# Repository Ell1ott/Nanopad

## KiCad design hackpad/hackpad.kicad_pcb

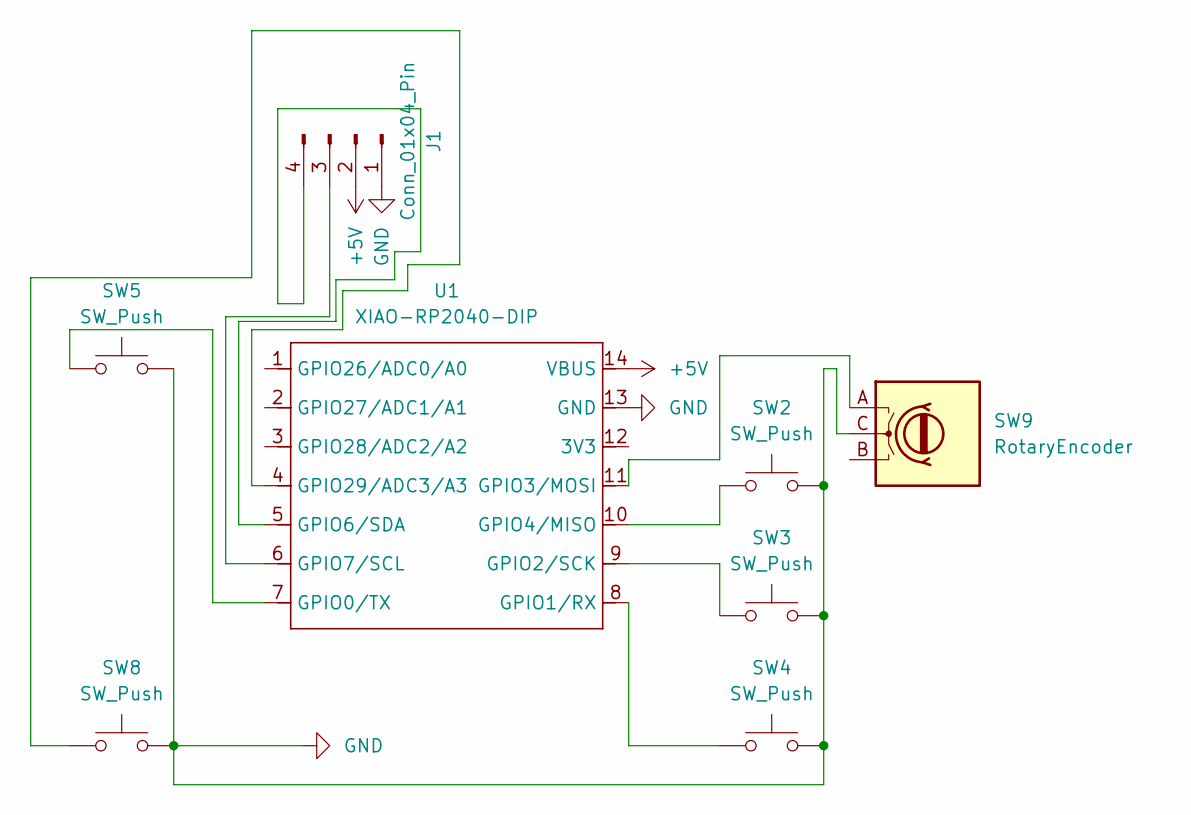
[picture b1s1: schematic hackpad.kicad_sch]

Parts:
J1: Conn_01x04_Pin; SSD1306-0.91-OLED-4pin-128x32
SW2, SW3, SW4, SW5, SW8: SW_Push; SW_Cherry_MX_1.00u_PCB
SW9: RotaryEncoder; RotaryEncoder_Alps_EC11E-Switch_Vertical_H20mm
U1: XIAO-RP2040-DIP

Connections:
+5V: J1.2, U1.14 (VBUS)
GND: J1.1, SW2.2, SW3.2, SW4.2, SW5.2, SW8.2, SW9.C, U1.13 (GND)
unnamed: J1.3, U1.6 (GPIO7/SCL)
unnamed: J1.4, U1.5 (GPIO6/SDA)
unnamed: SW5.1, U1.7 (GPIO0/TX)
unnamed: SW4.1, U1.8 (GPIO1/RX)
unnamed: SW3.1, U1.9 (GPIO2/SCK)
unnamed: SW9.A, U1.11 (GPIO3/MOSI)
unnamed: SW2.1, U1.10 (GPIO4/MISO)
unnamed: SW8.1, U1.4 (GPIO29/ADC3/A3)

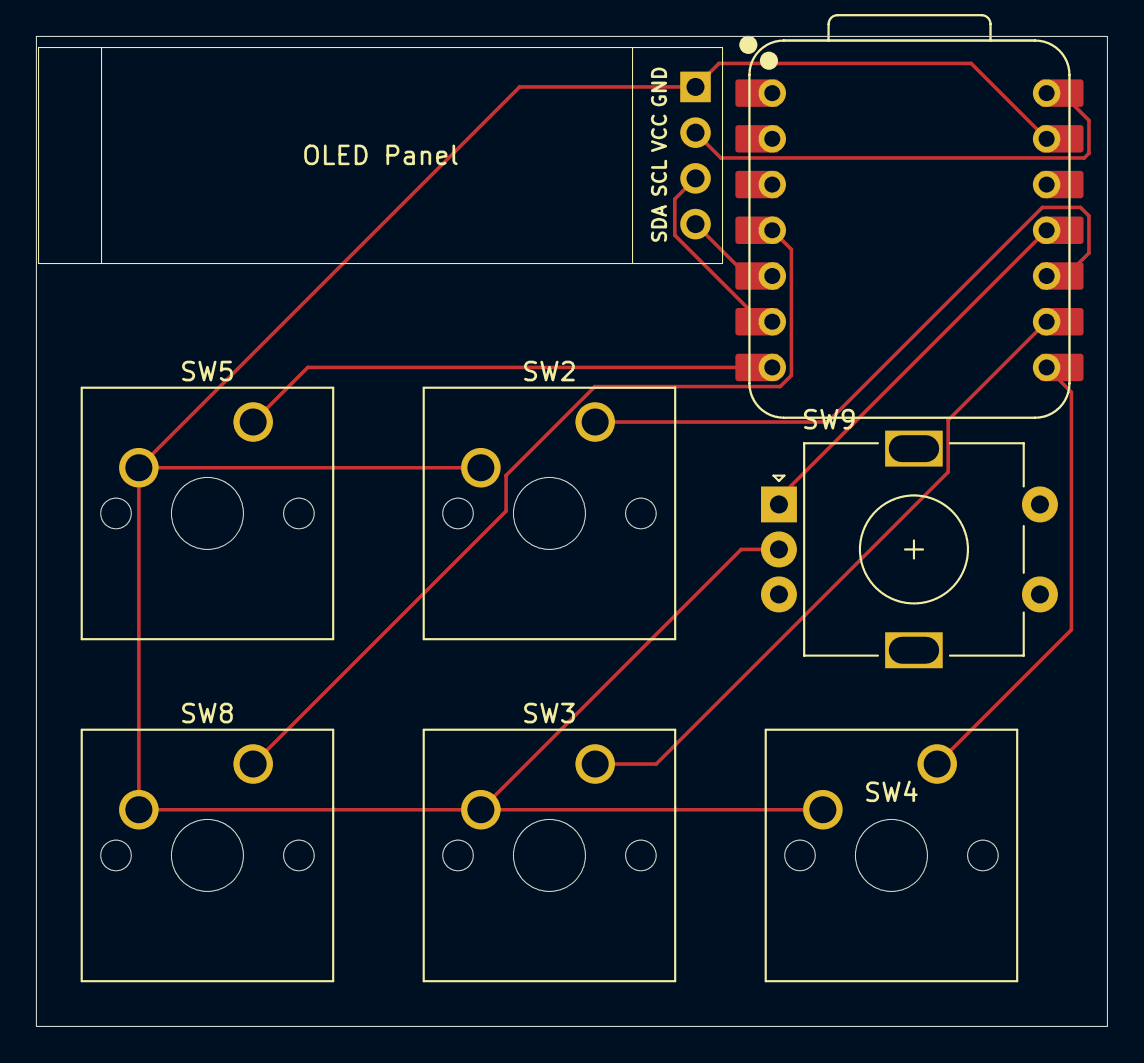
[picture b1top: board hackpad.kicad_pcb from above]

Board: 2 copper layers, 59.5 x 55.0 mm, 8 parts (0 on the bottom side), 10 nets.

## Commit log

2025-07-01 Add the hackpad
2025-07-01 Update fp-info-cache
